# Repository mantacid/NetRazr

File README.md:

This Documentation contains all the information you need to build and/or modify the NetRazr Cyberdeck.

This documentation was designed to be read in the Obsidian Application, and as such some formatting may be broken when viewed on Github. I will try my best to make the two as compatible as possible.

![[Netrazr-Render-Test.png]]

# What is NetRazr?
The NetRazr is a [Cyberdeck](https://cyberdeck.cafe/mix/what-is-a-cyberdeck), designed to be unique, modifiable, and accessible to makers. It was planned, designed, and built on a budget, making implementation extremely flexible. Is the Compute Module/carrier board too expensive? Tweak the case and swap them out for a regular Pi and a screen. In this way, this documentation straddles the line between a parts list and loose hardware standard.

# Why'd you make it?
I thought it was cool, and I was tired of coming up with ideas and not being able to bring them into reality. So I showed the concept to a friend, and we both decided to make it a real thing.

---

# SPECS:
- Quad-Core ARM Processor
- Up to 8GB RAM
- Optional eEMC storage
- Real-time clock powered by a seperate button-cell battery
- Ports:
	- 3 USB 2.0 Ports
	- 1 USB-C Port (for power)
	- HDMI Output
	- Gigabit Ethernet
	- MicroSD Card socket (for live images. I recommend learning to partition and format a disk, so you can use an SSD to contain the bulk of the OS. Micro SD cards tend to fail suddenly.)
	- 40 Pin GPIO
	- PoE Header
	- Fan Header
	- M.2 Slot for Optional SSD
- Built-in 5" Capacitive touch display (800x480 px)
- Split Mechanical Keyboard with custom layout and firmware
- Ample space inside for modding
- 3D-Printed casing with optional wrist support

# How do I Start?
Every piece of information you'll need to make this device is included in this repository, and sorted into directories for ease of location. You are free to customize, modify, and/or improve these designs to better fit your use-case, so long as you attribute me.

## Making the NetRazr your own
When making this device, you may come up with ideas to make the system better suited for specific cases, or you may find ways to improve the deck overall. If you have made a significant change to how the deck functions, I encourage you to fork this repository and detail the implemented changes. Make sure to link back to my original repository, as well as to the one you forked from (if those two aren't the same repository).

To start building this project for yourself, Follow the checklist below (in order).
## Progress Tracker
The following sections detail the creation of the base system:
- [ ] [[Components-List|Aquire all Components]]
- [ ] [[Create & Code the Keyboard]]
- [ ] [[Fabricate the Case]]
- [ ] [[Hardware Assembly]]
- [ ] Firmware Setup

The following are just a few ideas for modifications that could be implemented:
- A secondary display placed in a more traditional location
- Internet over GSM
- Hot-swappable Linux images
- A mounting bracket to use your phone as a monitor over VNC
- Using AA batteries as a backup power source for off-the-grid applications

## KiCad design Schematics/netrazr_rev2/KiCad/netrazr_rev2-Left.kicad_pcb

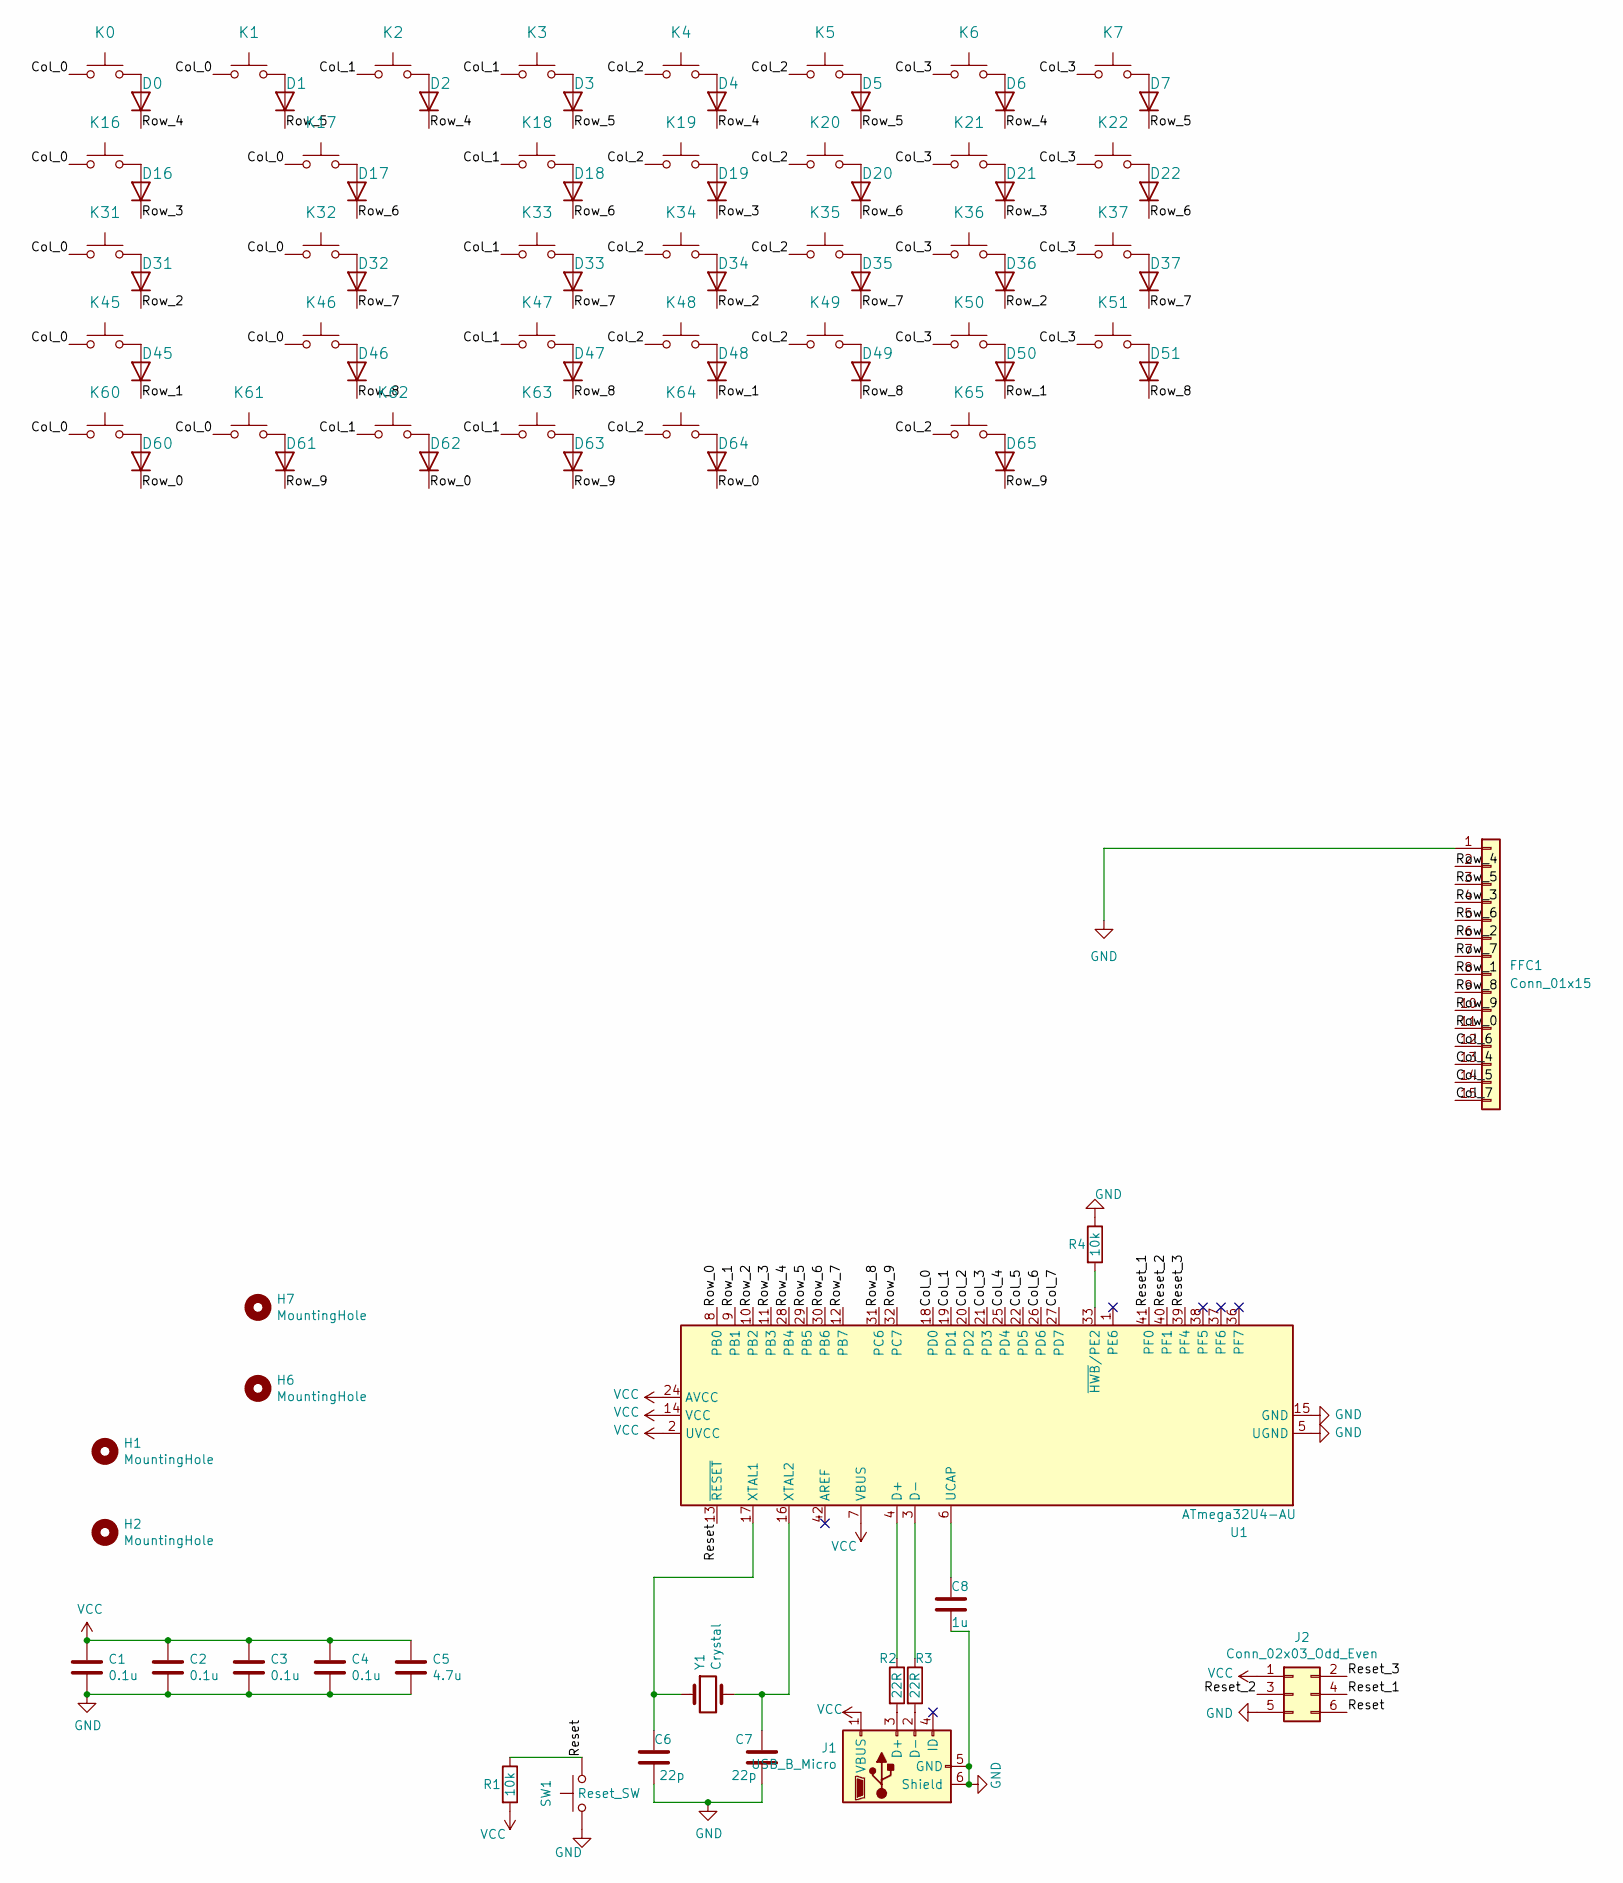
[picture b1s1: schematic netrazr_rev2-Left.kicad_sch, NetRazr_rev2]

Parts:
C1, C2, C3, C4: 0.1u; C_0805_2012Metric_Pad1.15x1.40mm_HandSolder
C5: 4.7u; C_0805_2012Metric_Pad1.15x1.40mm_HandSolder
C6, C7: 22p; C_0805_2012Metric_Pad1.15x1.40mm_HandSolder
C8: 1u; C_0805_2012Metric_Pad1.15x1.40mm_HandSolder
D0, D1, D2, D3, D4, D5, D6, D7, D16, D17, D18, D19, D20, D21, D22, D31, D32, D33, D34, D35, D36, D37, D45, D46, D47, D48, D49, D50, D51, D60, D61, D62, D63, D64, D65: D; D_0805_2012Metric_Pad1.15x1.40mm_HandSolder
FFC1: Conn_01x15; Hirose_FH12-15S-0.5SH_1x15-1MP_P0.50mm_Horizontal
H1, H2, H6, H7: MountingHole; MountingHole_3.2mm_M3_DIN965
J1: USB_B_Micro; USB_Micro-B_Wuerth_629105150521_CircularHoles
J2: Conn_02x03_Odd_Even; PinHeader_2x03_P2.54mm_Vertical
K0: MACRO,,,,,,1; Kailh_socket_PG1350
K1: ESC; Kailh_socket_PG1350
K2: ~~,,,,,,,,,`; Kailh_socket_PG1350
K3: !,,f1,,,,,,,1; Kailh_socket_PG1350
K4: @,,f2,,,,,,,2; Kailh_socket_PG1350
K5: #,,f3,,,,,,,3; Kailh_socket_PG1350
K6: $,,f4,,,,,,,4; Kailh_socket_PG1350
K7: %,,f5,,,,,,,5; Kailh_socket_PG1350
K16: MACRO,,,,,,2; Kailh_socket_PG1350
K17: TAB; Kailh_socket_PG1350
K18: Q; Kailh_socket_PG1350
K19: W; Kailh_socket_PG1350
K20: E; Kailh_socket_PG1350
K21: R; Kailh_socket_PG1350
K22: T; Kailh_socket_PG1350
K31: MACRO,,,,,,3; Kailh_socket_PG1350
K32: CAPS; Kailh_socket_PG1350
K33: A; Kailh_socket_PG1350
K34: S; Kailh_socket_PG1350
K35: D; Kailh_socket_PG1350
K36: F; Kailh_socket_PG1350
K37: G; Kailh_socket_PG1350
K45: MACRO,,,,,,4; Kailh_socket_PG1350
K46: LSHIFT; Kailh_socket_PG1350
K47: Z; Kailh_socket_PG1350
K48: X; Kailh_socket_PG1350
K49: C; Kailh_socket_PG1350
K50: V; Kailh_socket_PG1350
K51: B; Kailh_socket_PG1350
K60: MACRO,,,,,,5; Kailh_socket_PG1350
K61: LCTRL; Kailh_socket_PG1350
K62: FN; Kailh_socket_PG1350
K63: META; Kailh_socket_PG1350
K64: LALT; Kailh_socket_PG1350
K65: LSPACE; Kailh_socket_PG1350
R1, R4: 10k; R_0805_2012Metric_Pad1.15x1.40mm_HandSolder
R2, R3: 22R; R_0805_2012Metric_Pad1.15x1.40mm_HandSolder
SW1: Reset_SW; SW_Push_1P1T_NO_6x6mm_H9.5mm
U1: ATmega32U4-AU; TQFP-44_10x10mm_P0.8mm
Y1: Crystal; Crystal_SMD_5032-2Pin_5.0x3.2mm_HandSoldering

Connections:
/Col_0: K0.1, K1.1, K16.1, K17.1, K31.1, K32.1, K45.1, K46.1, K60.1, K61.1, U1.18 (PD0)
/Col_1: K2.1, K3.1, K18.1, K33.1, K47.1, K62.1, K63.1, U1.19 (PD1)
/Col_2: K4.1, K5.1, K19.1, K20.1, K34.1, K35.1, K48.1, K49.1, K64.1, K65.1, U1.20 (PD2)
/Col_3: K6.1, K7.1, K21.1, K22.1, K36.1, K37.1, K50.1, K51.1, U1.21 (PD3)
/Col_4: FFC1.13, U1.25 (PD4)
/Col_5: FFC1.14, U1.22 (PD5)
/Col_6: FFC1.12, U1.26 (PD6)
/Col_7: FFC1.15, U1.27 (PD7)
/Reset: J2.6, R1.1, SW1.2, U1.13 (~RESET)
/Row_0: D60.1 (K), D62.1 (K), D64.1 (K), FFC1.11, U1.8 (PB0)
/Row_4: D0.1 (K), D2.1 (K), D4.1 (K), D6.1 (K), FFC1.2, U1.28 (PB4)
/Row_5: D1.1 (K), D3.1 (K), D5.1 (K), D7.1 (K), FFC1.3, U1.29 (PB5)
/Row_6: D17.1 (K), D18.1 (K), D20.1 (K), D22.1 (K), FFC1.5, U1.30 (PB6)
/Row_7: D32.1 (K), D33.1 (K), D35.1 (K), D37.1 (K), FFC1.7, U1.12 (PB7)
/Row_8: D46.1 (K), D47.1 (K), D49.1 (K), D51.1 (K), FFC1.9, U1.31 (PC6)
/Row_9: D61.1 (K), D63.1 (K), D65.1 (K), FFC1.10, U1.32 (PC7)
GND: C1.2, C2.2, C3.2, C4.2, C5.2, C6.2, C7.2, C8.2, FFC1.1, J1.5 (GND), J1.6 (Shield), J2.5, R4.1, SW1.1, U1.5 (UGND), U1.15 (GND), U1.23 (GND), U1.35 (GND), U1.43 (GND)
unnamed: C6.1, U1.17 (XTAL1), Y1.1
unnamed: C7.1, U1.16 (XTAL2), Y1.2
unnamed: C8.1, U1.6 (UCAP)
unnamed: D0.2 (A), K0.2
unnamed: D1.2 (A), K1.2
unnamed: D2.2 (A), K2.2
unnamed: D3.2 (A), K3.2
unnamed: D4.2 (A), K4.2
unnamed: D5.2 (A), K5.2
unnamed: D6.2 (A), K6.2
unnamed: D7.2 (A), K7.2
unnamed: D16.2 (A), K16.2
unnamed: D17.2 (A), K17.2
unnamed: D18.2 (A), K18.2
unnamed: D19.2 (A), K19.2
unnamed: D20.2 (A), K20.2
unnamed: D21.2 (A), K21.2
unnamed: D22.2 (A), K22.2
unnamed: D31.2 (A), K31.2
unnamed: D32.2 (A), K32.2
unnamed: D33.2 (A), K33.2
unnamed: D34.2 (A), K34.2
unnamed: D35.2 (A), K35.2
unnamed: D36.2 (A), K36.2
unnamed: D37.2 (A), K37.2
unnamed: D45.2 (A), K45.2
unnamed: D46.2 (A), K46.2
unnamed: D47.2 (A), K47.2
unnamed: D48.2 (A), K48.2
unnamed: D49.2 (A), K49.2
unnamed: D50.2 (A), K50.2
unnamed: D51.2 (A), K51.2
unnamed: D60.2 (A), K60.2
unnamed: D61.2 (A), K61.2
unnamed: D62.2 (A), K62.2
unnamed: D63.2 (A), K63.2
unnamed: D64.2 (A), K64.2
unnamed: D65.2 (A), K65.2
unnamed: J1.2 (D-), R3.2
unnamed: J1.3 (D+), R2.2
unnamed: R2.1, U1.4 (D+)
unnamed: R3.1, U1.3 (D-)
unnamed: R4.2, U1.33 (~HWB/PE2)
VCC: C1.1, C2.1, C3.1, C4.1, C5.1, J1.1 (VBUS), J2.1, R1.2, U1.2 (UVCC), U1.7 (VBUS), U1.14 (VCC), U1.24 (AVCC), U1.34 (VCC), U1.44 (AVCC)

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
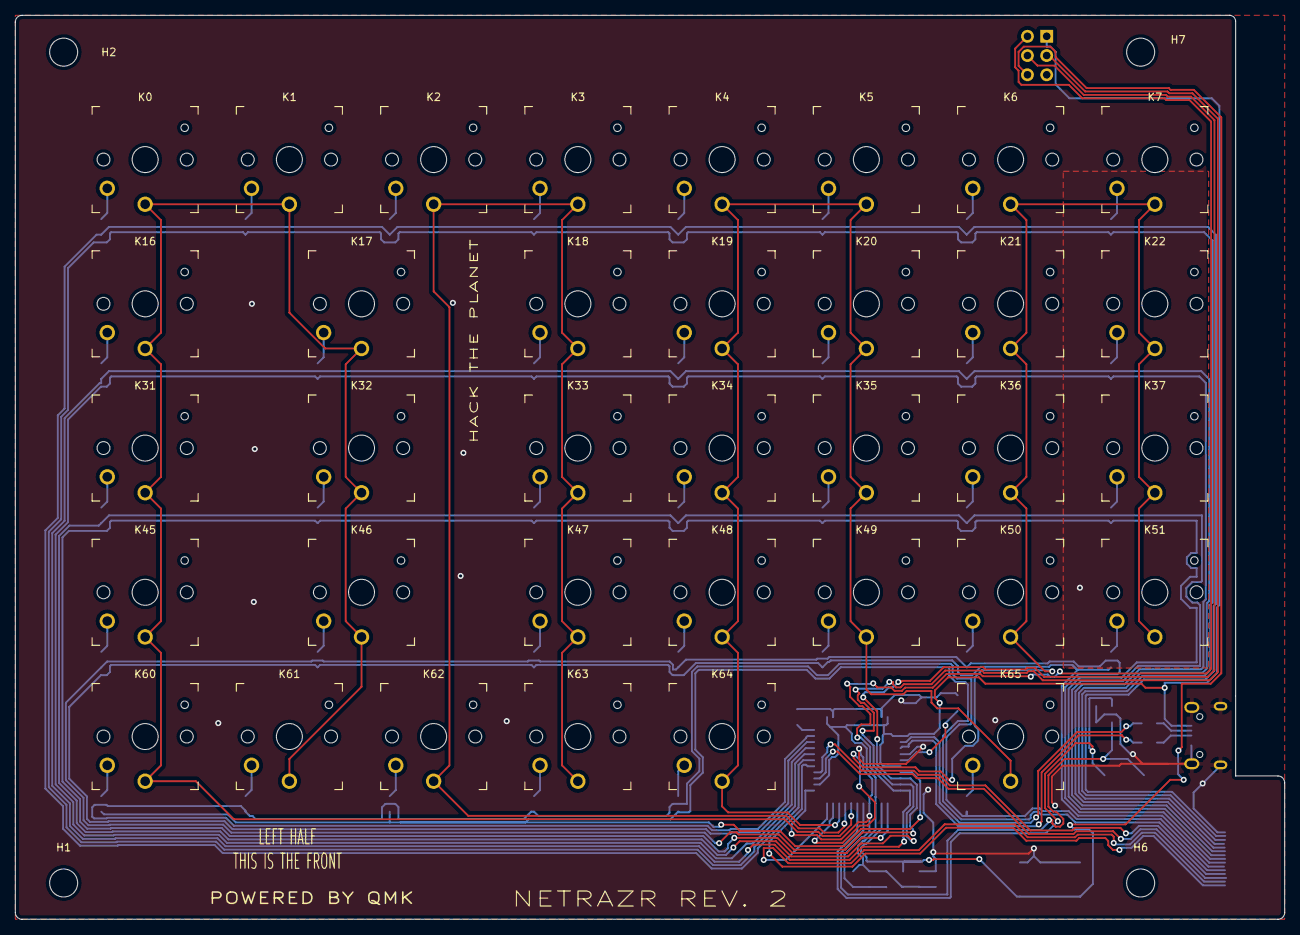
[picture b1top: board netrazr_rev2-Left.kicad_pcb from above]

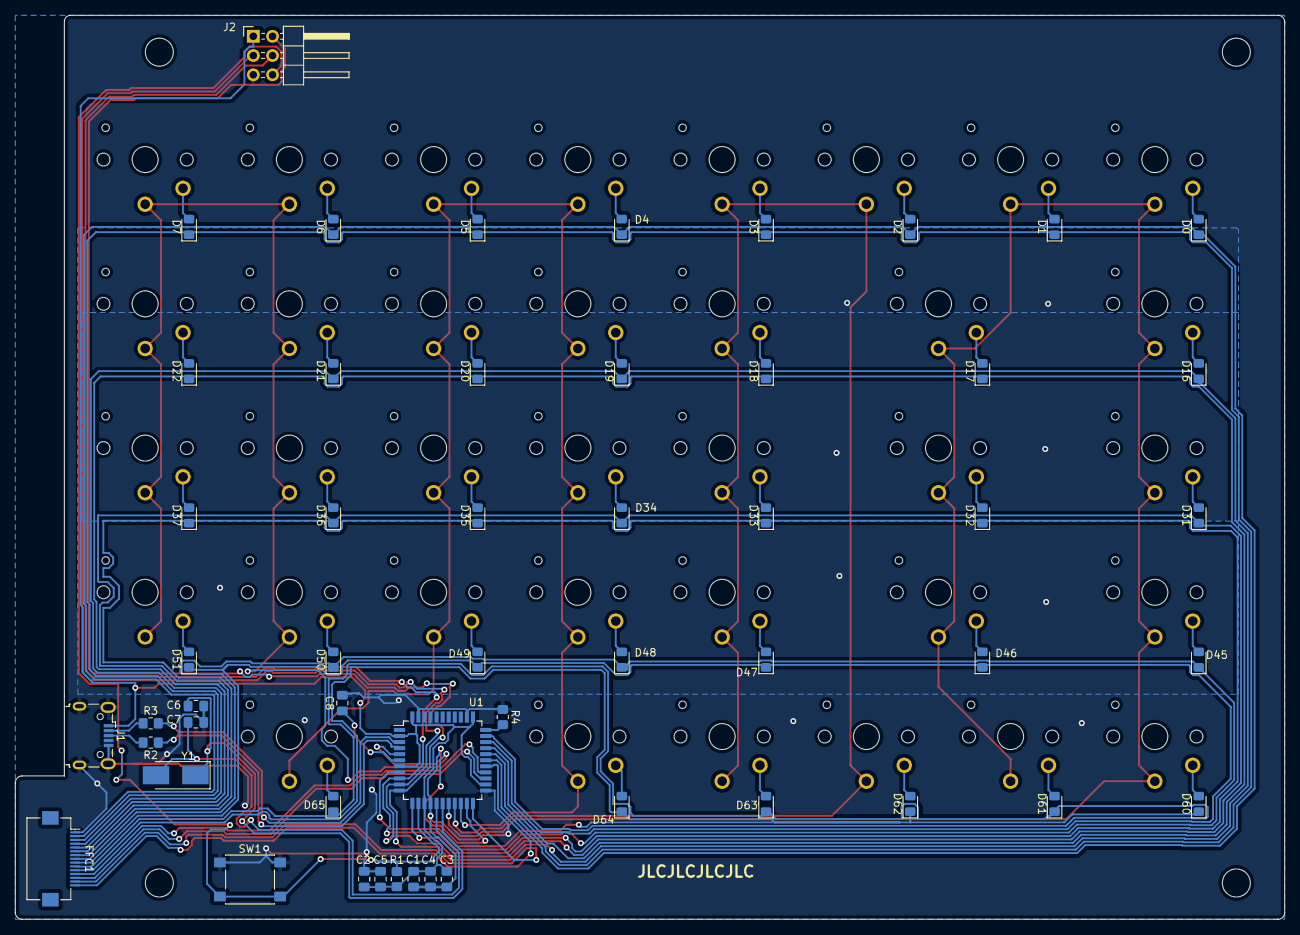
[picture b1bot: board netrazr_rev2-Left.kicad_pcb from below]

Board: 2 copper layers, 167.6 x 119.4 mm, 92 parts (53 on the bottom side), 64 nets.

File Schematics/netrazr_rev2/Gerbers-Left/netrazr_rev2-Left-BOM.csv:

"Id";"Designator";"Package";"Quantity";"Designation";"Supplier and ref";
1;"K48";"SW_PG1350_withKeyCap";1;"X";;;
2;"K1";"SW_PG1350_withKeyCap";1;"ESC";;;
3;"K7";"SW_PG1350_withKeyCap";1;"%,,f5,,,,,,,5";;;
4;"K6";"SW_PG1350_withKeyCap";1;"$,,f4,,,,,,,4";;;
5;"K63";"SW_PG1350_withKeyCap";1;"META";;;
6;"K45";"SW_PG1350_withKeyCap";1;"MACRO,,,,,,4";;;
7;"K51";"SW_PG1350_withKeyCap";1;"B";;;
8;"K49";"SW_PG1350_withKeyCap";1;"C";;;
9;"K0";"SW_PG1350_withKeyCap";1;"MACRO,,,,,,1";;;
10;"K17";"SW_PG1350_withKeyCap";1;"TAB";;;
11;"K18";"SW_PG1350_withKeyCap";1;"Q";;;
12;"K20";"SW_PG1350_withKeyCap";1;"E";;;
13;"K31";"SW_PG1350_withKeyCap";1;"MACRO,,,,,,3";;;
14;"K37";"SW_PG1350_withKeyCap";1;"G";;;
15;"K61";"SW_PG1350_withKeyCap";1;"LCTRL";;;
16;"K35";"SW_PG1350_withKeyCap";1;"D";;;
17;"K47";"SW_PG1350_withKeyCap";1;"Z";;;
18;"K62";"SW_PG1350_withKeyCap";1;"FN";;;
19;"K2";"SW_PG1350_withKeyCap";1;"~~,,,,,,,,,`";;;
20;"K16";"SW_PG1350_withKeyCap";1;"MACRO,,,,,,2";;;
21;"K46";"SW_PG1350_withKeyCap";1;"LSHIFT";;;
22;"K32";"SW_PG1350_withKeyCap";1;"CAPS";;;
23;"K65";"SW_PG1350_withKeyCap";1;"LSPACE";;;
24;"K19";"SW_PG1350_withKeyCap";1;"W";;;
25;"K64";"SW_PG1350_withKeyCap";1;"LALT";;;
26;"K3";"SW_PG1350_withKeyCap";1;"!,,f1,,,,,,,1";;;
27;"K33";"SW_PG1350_withKeyCap";1;"A";;;
28;"K60";"SW_PG1350_withKeyCap";1;"MACRO,,,,,,5";;;
29;"K22";"SW_PG1350_withKeyCap";1;"T";;;
30;"K21";"SW_PG1350_withKeyCap";1;"R";;;
31;"K34";"SW_PG1350_withKeyCap";1;"S";;;
32;"K4";"SW_PG1350_withKeyCap";1;"@,,f2,,,,,,,2";;;
33;"K5";"SW_PG1350_withKeyCap";1;"#,,f3,,,,,,,3";;;
34;"K36";"SW_PG1350_withKeyCap";1;"F";;;
35;"K50";"SW_PG1350_withKeyCap";1;"V";;;
36;"J1";"USB_Micro-B_Wuerth_629105150521";1;"USB_B_Micro";;;
37;"C2,C4,C3,C1";"C_0805_2012Metric_Pad1.18x1.45mm_HandSolder";4;"0.1u";;;
38;"J2";"PinHeader_2x03_P2.54mm_Horizontal";1;"Conn_02x03_Odd_Even";;;
39;"D64,D33,D5,D21,D35,D47,D37,D32,D19,D45,D61,D31,D63,D4,D62,D65,D51,D7,D48,D17,D50,D60,D20,D2,D36,D18,D16,D22,D6,D49,D34,D46,D3,D0,D1";"D_0805_2012Metric_Pad1.15x1.40mm_HandSolder";35;"D";;;
40;"SW1";"SW_Push_1P1T_NO_6x6mm_H9.5mm";1;"Reset_SW";;;
41;"C8";"C_0805_2012Metric_Pad1.18x1.45mm_HandSolder";1;"1u";;;
42;"R4,R1";"R_0805_2012Metric_Pad1.20x1.40mm_HandSolder";2;"10k";;;
43;"U1";"TQFP-44_10x10mm_P0.8mm";1;"ATmega32U4-AU";;;
44;"C5";"C_0805_2012Metric_Pad1.18x1.45mm_HandSolder";1;"4.7u";;;
45;"R2,R3";"R_0805_2012Metric_Pad1.20x1.40mm_HandSolder";2;"22R";;;
46;"Y1";"Crystal_SMD_5032-2Pin_5.0x3.2mm_HandSoldering";1;"Crystal";;;
47;"C6,C7";"C_0805_2012Metric_Pad1.18x1.45mm_HandSolder";2;"22p";;;
48;"FFC1";"Hirose_FH12-15S-0.5SH_1x15-1MP_P0.50mm_Horizontal";1;"Hirose_FH12-15S-0.5SH_1x15-1MP_P0.50mm_Horizontal";;;

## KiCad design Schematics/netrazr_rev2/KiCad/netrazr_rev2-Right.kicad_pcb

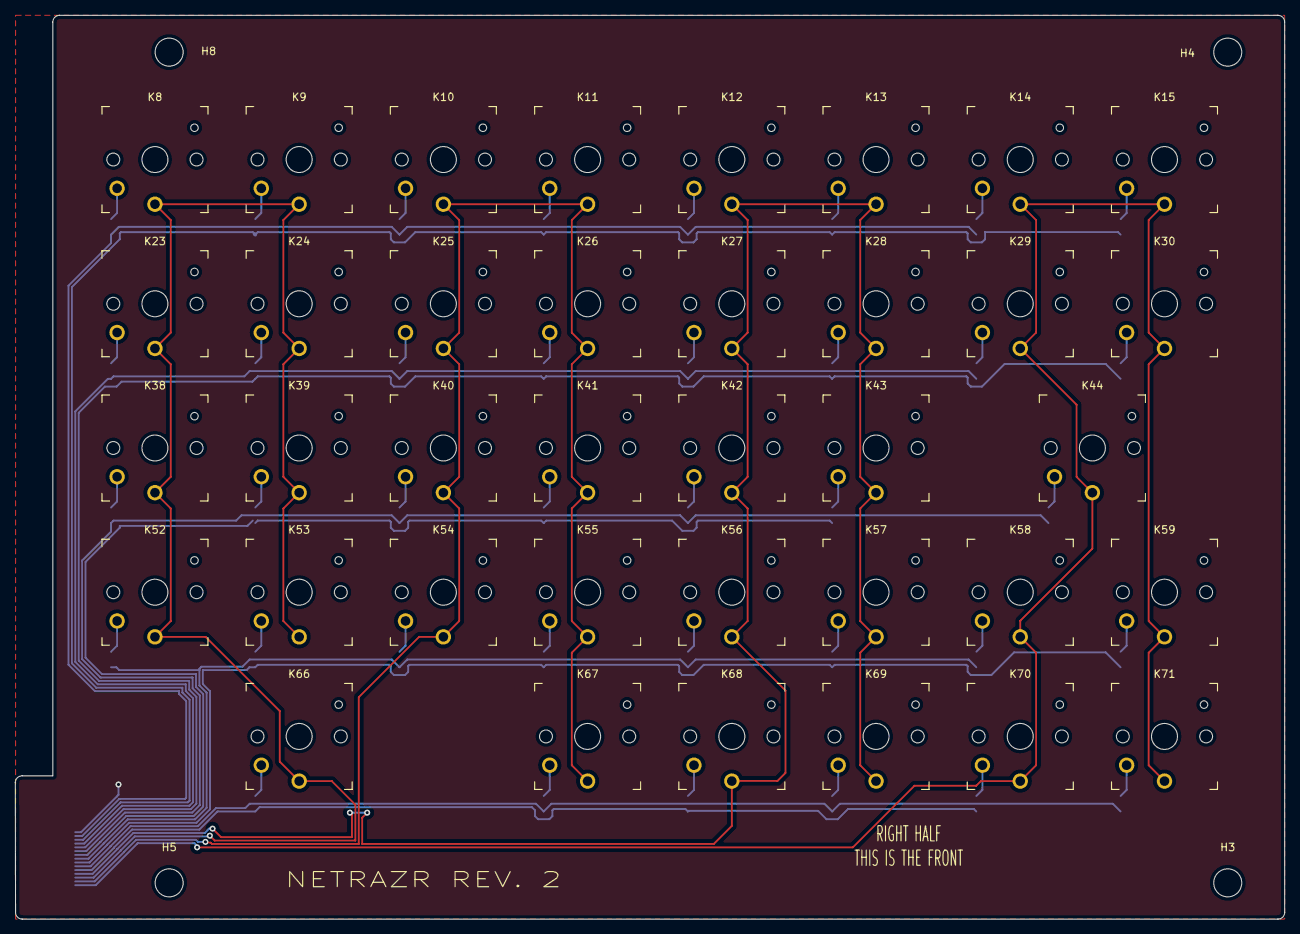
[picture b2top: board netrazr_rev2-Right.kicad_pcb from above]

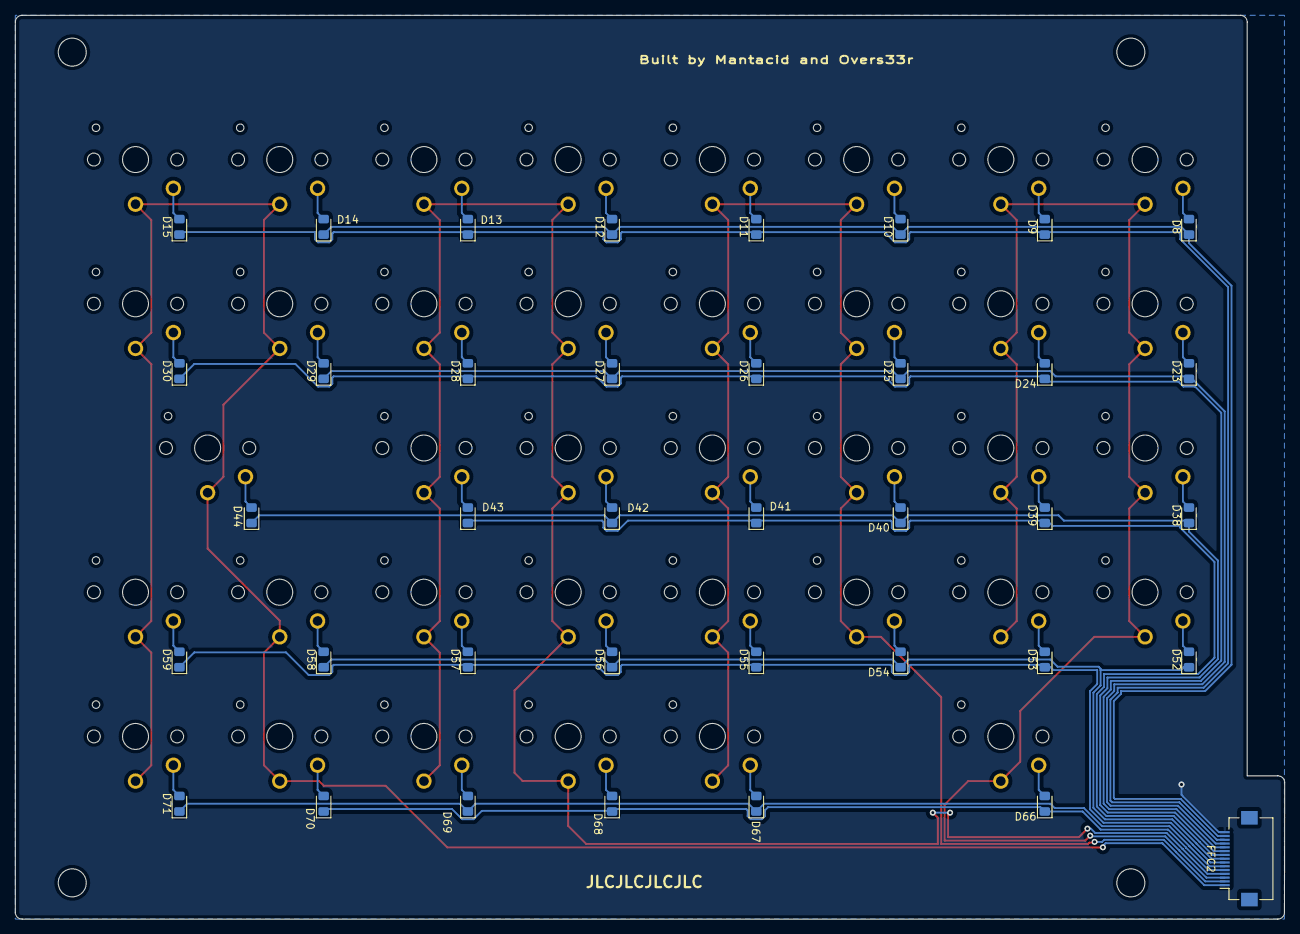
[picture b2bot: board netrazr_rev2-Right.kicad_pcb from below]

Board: 2 copper layers, 167.7 x 119.4 mm, 79 parts (38 on the bottom side), 51 nets.

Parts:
D8, D9, D10, D11, D12, D13, D14, D15, D23, D24, D25, D26, D27, D28, D29, D30, D38, D39, D40, D41, D42, D43, D44, D52, D53, D54, D55, D56, D57, D58, D59, D66, D67, D68, D69, D70, D71: D; D_0805_2012Metric_Pad1.15x1.40mm_HandSolder
FFC2: Hirose_FH12-15S-0.5SH_1x15-1MP_P0.50mm_Horizontal
H3, H4, H5, H8: MountingHole; MountingHole_3.7mm
K8: ^,,f6,,,,,,,6; SW_PG1350_withKeyCap
K9: &,,f7,,,,,,,7; SW_PG1350_withKeyCap
K10: *,,f8,,,,,,,8; SW_PG1350_withKeyCap
K11: (,,f9,,,,,,,9; SW_PG1350_withKeyCap
K12: ),,f10,,,,,,,0; SW_PG1350_withKeyCap
K13: _,,f11,,,,,,,-; SW_PG1350_withKeyCap
K14: +,,f12,,,,,,,=; SW_PG1350_withKeyCap
K15: BKSP; SW_PG1350_withKeyCap
K23: Y; SW_PG1350_withKeyCap
K24: U; SW_PG1350_withKeyCap
K25: I; SW_PG1350_withKeyCap
K26: O; SW_PG1350_withKeyCap
K27: P; SW_PG1350_withKeyCap
K28: {,,,,,,,,,[}; SW_PG1350_withKeyCap
K29: },,,,,,,,,]; SW_PG1350_withKeyCap
K30: |,,,,,,,,,\; SW_PG1350_withKeyCap
K38: H; SW_PG1350_withKeyCap
K39: J; SW_PG1350_withKeyCap
K40: K; SW_PG1350_withKeyCap
K41: L; SW_PG1350_withKeyCap
K42: :,,,,,,,,,;; SW_PG1350_withKeyCap
K43: ",,,,,,,,,'; SW_PG1350_withKeyCap
K44: ,,ENTER; SW_PG1350_withKeyCap
K52: N; SW_PG1350_withKeyCap
K53: M; SW_PG1350_withKeyCap
K54: <,,,,,,,,,,; SW_PG1350_withKeyCap
K55: >,,,,,,,,,.; SW_PG1350_withKeyCap
K56: ?,,,,,,,,,/; SW_PG1350_withKeyCap
K57: RSHIFT; SW_PG1350_withKeyCap
K58: UP; SW_PG1350_withKeyCap
K59: DEL; SW_PG1350_withKeyCap
K66: RSPACE; SW_PG1350_withKeyCap
K67: RALT; SW_PG1350_withKeyCap
K68: RCTRL; SW_PG1350_withKeyCap
K69: LEFT; SW_PG1350_withKeyCap
K70: DOWN; SW_PG1350_withKeyCap
K71: RIGHT; SW_PG1350_withKeyCap

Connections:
/Col_4: FFC2.3, K8.1, K9.1, K23.1, K24.1, K38.1, K39.1, K52.1, K53.1, K66.1
/Col_5: FFC2.2, K10.1, K11.1, K25.1, K26.1, K40.1, K41.1, K54.1, K55.1, K67.1
/Col_6: FFC2.4, K12.1, K13.1, K27.1, K28.1, K42.1, K43.1, K56.1, K57.1, K68.1, K69.1
/Col_7: FFC2.1, K14.1, K15.1, K29.1, K30.1, K44.1, K58.1, K59.1, K70.1, K71.1
/Row_0: D66.1 (K), D68.1 (K), D70.1 (K), FFC2.5
/Row_1: D52.1 (K), D54.1 (K), D56.1 (K), D58.1 (K), FFC2.8
/Row_2: D38.1 (K), D40.1 (K), D42.1 (K), D44.1 (K), FFC2.10
/Row_3: D23.1 (K), D25.1 (K), D27.1 (K), D29.1 (K), FFC2.12
/Row_4: D8.1 (K), D10.1 (K), D12.1 (K), D14.1 (K), FFC2.14
/Row_5: D9.1 (K), D11.1 (K), D13.1 (K), D15.1 (K), FFC2.13
/Row_6: D24.1 (K), D26.1 (K), D28.1 (K), D30.1 (K), FFC2.11
/Row_7: D39.1 (K), D41.1 (K), D43.1 (K), FFC2.9
/Row_8: D53.1 (K), D55.1 (K), D57.1 (K), D59.1 (K), FFC2.7
/Row_9: D67.1 (K), D69.1 (K), D71.1 (K), FFC2.6
unnamed: D8.2 (A), K8.2
unnamed: D9.2 (A), K9.2
unnamed: D10.2 (A), K10.2
unnamed: D11.2 (A), K11.2
unnamed: D12.2 (A), K12.2
unnamed: D13.2 (A), K13.2
unnamed: D14.2 (A), K14.2
unnamed: D15.2 (A), K15.2
unnamed: D23.2 (A), K23.2
unnamed: D24.2 (A), K24.2
unnamed: D25.2 (A), K25.2
unnamed: D26.2 (A), K26.2
unnamed: D27.2 (A), K27.2
unnamed: D28.2 (A), K28.2
unnamed: D29.2 (A), K29.2
unnamed: D30.2 (A), K30.2
unnamed: D38.2 (A), K38.2
unnamed: D39.2 (A), K39.2
unnamed: D40.2 (A), K40.2
unnamed: D41.2 (A), K41.2
unnamed: D42.2 (A), K42.2
unnamed: D43.2 (A), K43.2
unnamed: D44.2 (A), K44.2
unnamed: D52.2 (A), K52.2
unnamed: D53.2 (A), K53.2
unnamed: D54.2 (A), K54.2
unnamed: D55.2 (A), K55.2
unnamed: D56.2 (A), K56.2
unnamed: D57.2 (A), K57.2
unnamed: D58.2 (A), K58.2
unnamed: D59.2 (A), K59.2
unnamed: D66.2 (A), K66.2
unnamed: D67.2 (A), K67.2
unnamed: D68.2 (A), K68.2
unnamed: D69.2 (A), K69.2
unnamed: D70.2 (A), K70.2
unnamed: D71.2 (A), K71.2

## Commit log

2023-01-22 Create LICENSE
2023-01-22 Initial Commit
    Uploading a WIP Version of the repo to share it with my colleague.
2023-01-22 fixed gitignore
    forgot to make the gitignore before initial commit, so i had to remove some folders.
2023-01-29 fix PCB Mount placement, updated 3d model
    fixed the size and placement of the mounting holes.
    updated the 3d model of the pcb to better plan component spacing.
    todo: add support columns to 3d model to support bolts, figure out how case will disassemble.
2023-01-31 Fixed Keyswitch Footprints and modified component placement
    made the board not look like it was designed by a fish. may have to change the component footprints for easier soldering later.
    Also replaced the Power supply, As i have been informed that the one I had planned to use was not to be trusted.
    To Do:
    -finish 3d model
    -figure out how to reduce size of carrier board
    -add wrist support
2023-02-01 fixed length of D+ and D- Traces, case progress.
    reorganized traces and optimized the board layout. Make no mistake, it still looks bad. but at least its not as bad as it was.
    I also made progress on the case, adding a hole to route cables from the side compartments into the main body.
    note that fpr some reason the measurements for the inside are all screwed up, and a lot of things arent at 90 degree angles. I hope to fix that soon. for now though, any discrepancies in length are u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
2023-02-02 fixed kb layout grid, trimmed board
    hope this doesn't come back to bite me in the butt later.
2023-02-03 removed KiCad Backup directory from repo, added that directory to .gitignore
2023-02-03 Preparing Gerbers and related files files for Fabrication
2023-02-04 Split Case in two, Added holes for screws
    todo: add recesses for magnets, embedded nuts
    add mounting point for rails, figure out how to keep them open without overpowering the magnets.
2023-02-04 Minor fixes, added tools to make later steps easier
    added vertex groups to blend file to adjust the thickness of the deck.
    added tolerance gap between two halves of the casing.
2023-02-04 Added cutouts for embedded Nuts, hinge cutout for secondary display,, and fixed various things.
    -Added cutouts for Embedded Nuts (i have yet to find part numbers for those, so if anyone knows what to call the square nuts in the 12-in-1 Erector/Meccano Crane set than please tell me.
    -After waking up at 1 in the morning in a cold sweat, I realized that you'd need to remove part of the top case halves to slide the Keyboard PCBs in. those parts are now removable, and should frictio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
    -fixed the transform handle being broken upon applying the symmetry modifiers.
    to do:
    -design rail system
2023-02-05 Updated Documentation to better reflect my growing insanity
    - Added more detail about how the case fits together
    - pebis
2023-02-06 Updated Documentation to reflect changes in design
    I'm going to try printing the sliding rails rather than fasten some drawer slides, so I changed the materials list and docs to reflect this.
2023-02-09 adjusted clearances in model, updated docs
    changed thickness of deck to take advantage of a reduced carrier board size (I'll need to mod it tho), and added the embedded nuts to the rail system.
    also updated the documentation to specify materials and the various considerations taken into account.
    Linked to resources detailing precise dimensions for the metal components used in the deck.
2023-02-11 updated model to make room for more components, updated docs
    included board modding instructions, modeled the track that limits the motion of the rails.
    the carrier board turned out to have what seems like a custom ethernet port with four extra pins. I'm still trying to figure it out.
2023-02-11 added shape keys for wrist support.
    Casing components now have geometry that supports the addition of wrist supports. These can be toggled/adjusted via shape keys.
    Slots for the metal strips have also been added to the bottom of the casing.
    todo:
    -add holes for magnets
    -add mounting points for secondary display
    -remake the side covers for the third time.
2023-02-12 adjusted the spacing of bottom cutouts to allow for more strips to be mounted on the bottom
    this change will help you to secure additional modifications to the exterior of the case, such as a secondary display, a tripod mount, a shoulder strap, etc.
2023-02-12 Added sections on hwo to mod the ethernet port
2023-02-13 added key mockups
2023-02-15 added holes for rail magnets; removed wrist support shapekeys
    In order to use Boolean modifiers to add the magnet holes, I had to get rid of the shape keys and make two separate versions of the model. I'll try to reimplement them if possible.
2023-02-15 refined Keycap model, moved original to models directory
    you'll find 1U, 2U, and 3U keycaps in the wrist support blend file, since I used that to test the Measurements.
2023-02-15 Update LICENSE
2023-02-15 Add files via upload
    Refined keycap with simplistic design.
2023-02-16 still tweaking the keycaps
2023-02-16 finished adding magnet holes.
    still need to add mounting points for carrier board.
2023-02-18 Filed Out keycaps in model to prepare for rendering instructional diagrams
2023-02-18 brainstormed what to use for power, solved space constraints
    figured out how thick the display was and repositioned the carrier board accordingly. updated the docs to record the changes.
2023-02-19 added port holes, fixed docs to use correct power switch
    todo:
    -add mount holes for power board
    -make holes for charging port and button
    -modify rail system to take advantage of screen adhesive.
2023-02-20 added geometry to support mounting the screen via adhesive layer
    I'm still not comfortable with how close the screen is to the bottom of the keyboard. I'll try to move the upper plate up next commit. if that doesnt work I need to see how much i can thin the carrie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
2023-02-20 Adjusted height of Keyboard by 2mm
    proper clearance has been achieved. still need to add the USB-C charging port to the port plate cutouts, and I still need to create a mounting point for the UPS. I did, however, add a cutout for the 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
2023-02-20 added area for power board and battery
    At this point in the project, Delirium was setting in.
    I've marked out where (maybe) ill put some snap-fit connectors that will hold the power board in place. I had to sink it down a bit to fit the battery on top.
2023-02-20 minor topology fix
2023-02-20 added slots for embedded M2.5 Nut to mount the power board.
    Booleans have not been applied yet In case I need to move the board.
    may consider doing the same for the carrier board, depending on how the dimensions work out.
2023-02-20 edited docs
    fixed some typos, updated old info, and added links to get keycaps since 3d printing them ourselves didn't work too well.
2023-02-21 added links and geometry for USB-C charging port.
    I sprung for plate-mount, since I was NOT wiring a port to be flush with the surface.
2023-02-22 added vents for airflow.
2023-02-24 added place to route audio card, Polished Topology, QOL geometry
    Added a small gap in the left compartment cover to allow you to route earbuds through the case.
    added a friction-fit spot for the USB Audio card.
    Applied all booleans.
    Triangulated all case components on model with wrist support.
2023-02-26 slight geometry fixes
    seperated the cover and port plate pairs.
2023-02-26 corrected firmware to use the correct microcontroller
2023-02-27 Added additional geometry to wrist supports
    I realized that the case would be light enough taht any attempt to use the wrist support would tip the deck towards you, so I added some small stabilizing legs to prevent that from happening.
2023-02-27 added shader to use for instruction diagrams, added GPIO slot in port plate
2023-02-27 fixed rail alignment, added image to documentation
2023-02-28 reversed Covers
    I had put the covers on the wrong sides (the one with the gap was supposed to be on the side with the audio card). A simple mirror fixed the issue.
2023-03-05 added Firmware Hex File, altered Model Shader.
    To make your lives easier I compiled the Keyboard firmware myself, so all you have to do is flash it if you don't want to make any changes to the keyboard layout.
2023-03-07 Added Cable Slot To other cover
2023-03-12 Finished Assembly instructions.
    Also updated links to said pages.
2023-03-12 Update Components-List.md
    forgot a link
2023-03-12 Whoops forgot a step
    Added the step where you attach the compute module.
2023-03-25 forgot about the bootloader.
    also corrected the directory that should be placed in the qmk_firmware/keyboards folder
2023-04-01 corrected clock properties
    accidentally linked to 20Mhz clock instead of 16Mhz clock that the MCU calls for.
2023-04-01 Update Hardware Assembly.md
    you actually dont need to flash the firmware, as it comes on the microcontroller.
2023-04-09 adjusted dimensions to fit m.2 slot.
    The STEP file for the display board did not have the right dimensions for the m.2 slot. I had to squeeze some extra room to make it barely fit.
2023-04-11 added production firmware file
    i hope flashing this lets me bypass having to use the amtel dfu bootloader. Still trying to diagnose issues with the keyboard.
2023-09-16 Cut files to fit on Ender 3 220mm x 220mm print bed.
2023-09-16 Fixed typo, updated recommended protocol for setting up OS
    Since my last regular commits to this project, I learned how to install arch, which frees me from the Raspberry's microSD card booting.
